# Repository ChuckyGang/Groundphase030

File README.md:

# Groundphase030

This is my test of doing a very VERY simple 030 card for the Amiga 3000/4000 (only tested on 4000)
It breaks all designrules there is.  This is/was just a proof of concept.

it REQUIRES a FPU installed.

Produce cards if you like to or do stuff with this. but please.. OPEN!

Note, this IS a 4 layer board!

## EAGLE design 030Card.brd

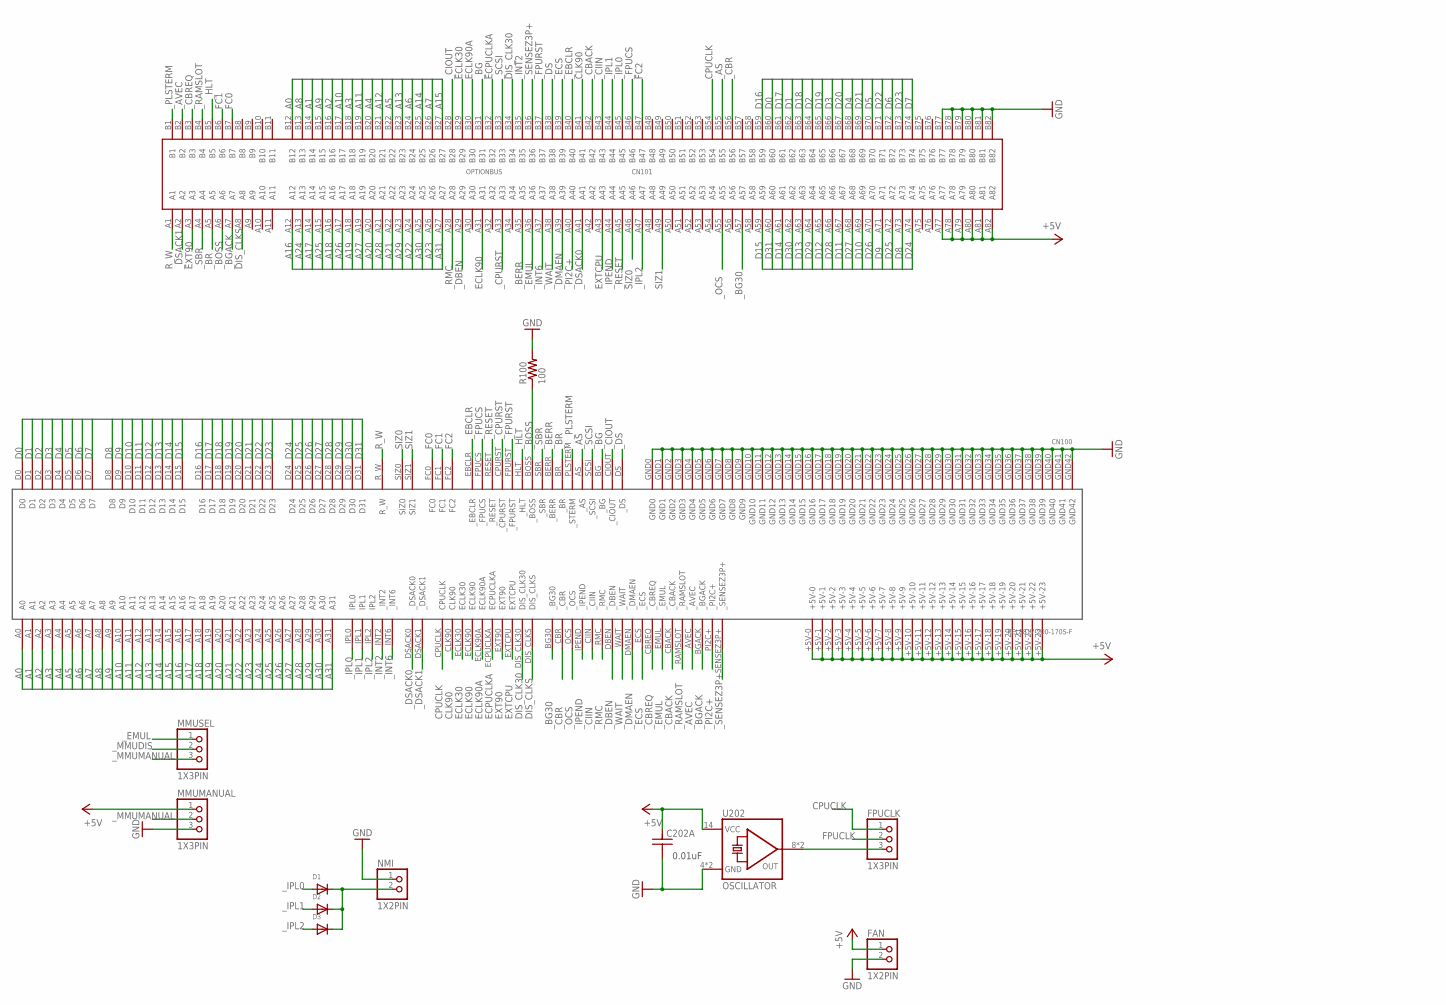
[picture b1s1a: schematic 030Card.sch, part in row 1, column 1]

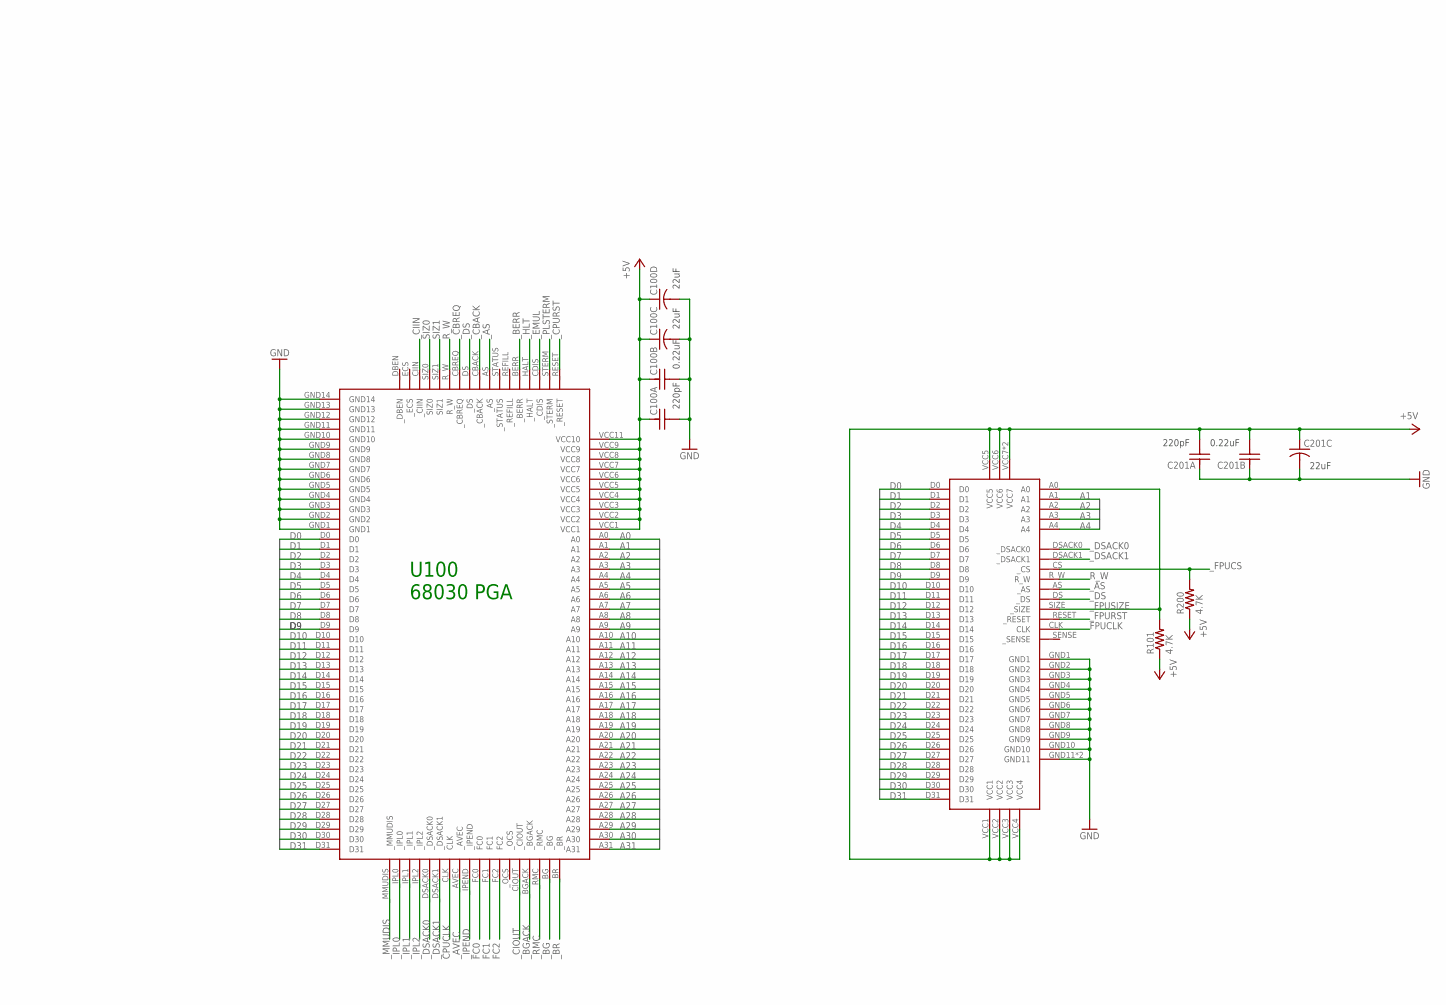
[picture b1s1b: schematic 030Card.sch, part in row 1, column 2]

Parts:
C100A, C201A: 220pF; R0805
C100B, C201B: 0.22uF; R0805
C100C, C100D, C201C: 22uF; SMD-ELECTROLYTE
C202A: 0.01uF; R0805
CN100: KEL8817-200-170S-F
CN101: OPTIONBUS
D1, D2, D3: DIODESOD-323F; SOD-323F
FAN: 1X2PIN
FPUCLK: 1X3PIN
MMUMANUAL: 1X3PIN
MMUSEL: 1X3PIN
NMI: 1X2PIN
R100: 100; R0805
R101, R200: 4.7K; R0805
U100: M68030
U201: M68882PLCC
U202: OSCILLATOR

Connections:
+5V: C100A.1, C100B.1, C100C.+ (1), C100D.+ (1), C201A.2, C201B.2, C201C.+ (1), C202A.1, CN100.+5V-0, CN100.+5V-1, CN100.+5V-2, CN100.+5V-3, CN100.+5V-4, CN100.+5V-5, CN100.+5V-6, CN100.+5V-7, CN100.+5V-8, CN100.+5V-9, CN100.+5V-10, CN100.+5V-11, CN100.+5V-12, CN100.+5V-13, CN100.+5V-14, CN100.+5V-15, CN100.+5V-16, CN100.+5V-17, CN100.+5V-18, CN100.+5V-19, CN100.+5V-20, CN100.+5V-21, CN100.+5V-22, CN100.+5V-23, CN101.A77, CN101.A78, CN101.A79, CN101.A80, CN101.A81, CN101.A82, FAN.1, MMUMANUAL.1, R101.1, R200.1, U100.VCC1, U100.VCC2, U100.VCC3, U100.VCC4, U100.VCC5, U100.VCC6, U100.VCC7, U100.VCC8, U100.VCC9, U100.VCC11 (VCC10), U201.VCC1, U201.VCC2, U201.VCC3, U201.VCC4, U201.VCC5, U201.VCC6, U201.VCC7, U201.VCC8 (VCC7), U202.14 (+5V)
A0: CN100.A0, CN101.B12, U100.A0
A1: CN100.A1, CN101.B14, U100.A1, U201.A1
A2: CN100.A2, CN101.B16, U100.A2, U201.A2
A3: CN100.A3, CN101.B18, U100.A3, U201.A3
A4: CN100.A4, CN101.B20, U100.A4, U201.A4
A5: CN100.A5, CN101.B22, U100.A5
A6: CN100.A6, CN101.B24, U100.A6
A7: CN100.A7, CN101.B26, U100.A7
A8: CN100.A8, CN101.B13, U100.A8
A9: CN100.A9, CN101.B15, U100.A9
A10: CN100.A10, CN101.B17, U100.A10
A11: CN100.A11, CN101.B19, U100.A11
A12: CN100.A12, CN101.B21, U100.A12
A13: CN100.A13, CN101.B23, U100.A13
A14: CN100.A14, CN101.B25, U100.A14
A15: CN100.A15, CN101.B27, U100.A15
A16: CN100.A16, CN101.A12, U100.A16
A17: CN100.A17, CN101.A14, U100.A17
A18: CN100.A18, CN101.A16, U100.A18
A19: CN100.A19, CN101.A18, U100.A19
A20: CN100.A20, CN101.A20, U100.A20
A21: CN100.A21, CN101.A22, U100.A21
A22: CN100.A22, CN101.A24, U100.A22
A23: CN100.A23, CN101.A26, U100.A23
A24: CN100.A24, CN101.A13, U100.A24
A25: CN100.A25, CN101.A15, U100.A25
A26: CN100.A26, CN101.A17, U100.A26
A27: CN100.A27, CN101.A19, U100.A27
A28: CN100.A28, CN101.A21, U100.A28
A29: CN100.A29, CN101.A23, U100.A29
A30: CN100.A30, CN101.A25, U100.A30
A31: CN100.A31, CN101.A27, U100.A31
CLK90: CN100.CLK90, CN101.B41
CPUCLK: CN100.CPUCLK, CN101.B54, FPUCLK.1, U100.CLK
D0: CN100.D0, CN101.B60, U100.D0, U201.D0
D1: CN100.D1, CN101.B62, U100.D1, U201.D1
D2: CN100.D2, CN101.B64, U100.D2, U201.D2
D3: CN100.D3, CN101.B66, U100.D3, U201.D3
D4: CN100.D4, CN101.B68, U100.D4, U201.D4
D5: CN100.D5, CN101.B70, U100.D5, U201.D5
D6: CN100.D6, CN101.B72, U100.D6, U201.D6
D7: CN100.D7, CN101.B74, U100.D7, U201.D7
D8: CN100.D8, CN101.A73, U100.D8, U201.D8
D9: CN100.D9, CN101.A71, U100.D9, U201.D9
D10: CN100.D10, CN101.A69, U100.D10, U201.D10
D11: CN100.D11, CN101.A67, U100.D11, U201.D11
D12: CN100.D12, CN101.A65, U100.D12, U201.D12
D13: CN100.D13, CN101.A63, U100.D13, U201.D13
D14: CN100.D14, CN101.A61, U100.D14, U201.D14
D15: CN100.D15, CN101.A59, U100.D15, U201.D15
D16: CN100.D16, CN101.B59, U100.D16, U201.D16
D17: CN100.D17, CN101.B61, U100.D17, U201.D17
D18: CN100.D18, CN101.B63, U100.D18, U201.D18
D19: CN100.D19, CN101.B65, U100.D19, U201.D19
D20: CN100.D20, CN101.B67, U100.D20, U201.D20
D21: CN100.D21, CN101.B69, U100.D21, U201.D21
D22: CN100.D22, CN101.B71, U100.D22, U201.D22
D23: CN100.D23, CN101.B73, U100.D23, U201.D23
D24: CN100.D24, CN101.A74, U100.D24, U201.D24
D25: CN100.D25, CN101.A72, U100.D25, U201.D25
D26: CN100.D26, CN101.A70, U100.D26, U201.D26
D27: CN100.D27, CN101.A68, U100.D27, U201.D27
D28: CN100.D28, CN101.A66, U100.D28, U201.D28
D29: CN100.D29, CN101.A64, U100.D29, U201.D29
D30: CN100.D30, CN101.A62, U100.D30, U201.D30
D31: CN100.D31, CN101.A60, U100.D31, U201.D31
DIS_CLK30: CN100.DIS_CLK30, CN101.B34
DIS_CLKS: CN100.DIS_CLKS, CN101.A8
ECLK30: CN100.ECLK30, CN101.B29
ECLK90: CN100.ECLK90, CN101.A31
ECLK90A: CN100.ECLK90A, CN101.B30
ECPUCLKA: CN100.ECPUCLKA, CN101.B32
EXT90: CN100.EXT90, CN101.A3
EXTCPU: CN100.EXTCPU, CN101.A43
EXTFPUCLK: FPUCLK.3, U202.8 (OUT), U202.11 (OUT)
FC0: CN100.FC0, CN101.B7, U100.FC0
FC1: CN100.FC1, CN101.B6, U100.FC1
FC2: CN100.FC2, CN101.B47, U100.FC2
FPUCLK: FPUCLK.2, U201.CLK
GND: C100A.2, C100B.2, C100C.- (2), C100D.- (2), C201A.1, C201B.1, C201C.- (2), C202A.2, CN100.GND0, CN100.GND1, CN100.GND2, CN100.GND3, CN100.GND4, CN100.GND5, CN100.GND6, CN100.GND7, CN100.GND8, CN100.GND9, CN100.GND10, CN100.GND11, CN100.GND12, CN100.GND13, CN100.GND14, CN100.GND15, CN100.GND16, CN100.GND17, CN100.GND18, CN100.GND19, CN100.GND20, CN100.GND21, CN100.GND22, CN100.GND23, CN100.GND24, CN100.GND25, CN100.GND26, CN100.GND27, CN100.GND28, CN100.GND29, CN100.GND30, CN100.GND31, CN100.GND32, CN100.GND33, CN100.GND34, CN100.GND35, CN100.GND36, CN100.GND37, CN100.GND38, CN100.GND39, CN100.GND40, CN100.GND41, CN100.GND42, CN101.B77, CN101.B78, CN101.B79, CN101.B80, CN101.B81, CN101.B82, FAN.2, MMUMANUAL.3, NMI.1, R100.2, U100.GND1, U100.GND2, U100.GND3, U100.GND4, U100.GND5, U100.GND6, U100.GND7, U100.GND8, U100.GND9, U100.GND10, U100.GND11, U100.GND12, U100.GND13, U100.GND14, U201.GND1, U201.GND2, U201.GND3, U201.GND4, U201.GND5, U201.GND6, U201.GND7, U201.GND8, U201.GND9, U201.GND10, U201.GND11, U201.GND12 (GND11), U202.4 (GND), U202.7 (GND)
R_W: CN100.R_W, CN101.A1, U100.R_W, U201.R_W
SIZ0: CN100.SIZ0, CN101.A46, U100.SIZ0
SIZ1: CN100.SIZ1, CN101.A49, U100.SIZ1
_AS: CN100._AS, CN101.B55, U100._AS, U201._AS
_AVEC: CN100._AVEC, CN101.B2, U100._AVEC
_BERR: CN100._BERR, CN101.A35, U100._BERR
_BG: CN100._BG, CN101.B31, U100._BG
_BG30: CN100._BG30, CN101.A57
_BGACK: CN100._BGACK, CN101.A7, U100._BGACK
_BOSS: CN100._BOSS, CN101.A6, R100.1
_BR: CN100._BR, CN101.A5, U100._BR
_CBACK: CN100._CBACK, CN101.B42, U100._CBACK
_CBR: CN100._CBR, CN101.B56
_CBREQ: CN100._CBREQ, CN101.B3, U100._CBREQ
_CIIN: CN100._CIIN, CN101.B43, U100._CIIN
_CIOUT: CN100._CIOUT, CN101.B28, U100._CIOUT
_CPURST: CN100._CPURST, CN101.A33, U100._RESET
_DBEN: CN100._DBEN, CN101.A29
_DMAEN: CN100._DMAEN, CN101.A39
_DS: CN100._DS, CN101.B38, U100._DS, U201._DS
_DSACK0: CN100._DSACK0, CN101.A41, U100._DSACK0, U201._DSACK0
_DSACK1: CN100._DSACK1, CN101.A2, U100._DSACK1, U201._DSACK1
_EBCLR: CN100._EBCLR, CN101.B40
_ECS: CN100._ECS, CN101.B39
_EMUL: CN100._EMUL, CN101.A36, MMUSEL.1, U100._CDIS
_FPUCS: CN100._FPUCS, CN101.B46, R200.2, U201._CS
_FPURST: CN100._FPURST, CN101.B37, U201._RESET
_FPUSIZE: R101.2, U201.A0, U201.SIZE (_SIZE)
_HLT: CN100._HLT, CN101.B5, U100._HALT
_INT2: CN100._INT2, CN101.B35
_INT6: CN100._INT6, CN101.A37
_IPEND: CN100._IPEND, CN101.A44, U100._IPEND
_IPL0: CN100._IPL0 (IPL0), CN101.B45, D1.A, U100._IPL0
_IPL1: CN100._IPL1 (IPL1), CN101.B44, D2.A, U100._IPL1
_IPL2: CN100._IPL2 (IPL2), CN101.A47, D3.A, U100._IPL2
_MMUDIS: MMUSEL.2, U100._MMUDIS
_MMUMANUAL: MMUMANUAL.2, MMUSEL.3
_NMI: D1.C, D2.C, D3.C, NMI.2
_OCS: CN100._OCS, CN101.A55
_PI2C+: CN100._PI2C+, CN101.A40
_PLSTERM: CN100._PLSTERM (_STERM), CN101.B1, U100._STERM
_RAMSLOT: CN100._RAMSLOT, CN101.B4
_RESET: CN100._RESET, CN101.A45
_RMC: CN100._RMC, CN101.A28, U100._RMC
_SBR: CN100._SBR, CN101.A4
_SCSI: CN100._SCSI, CN101.B33
_SENSEZ3P+: CN100._SENSEZ3P+, CN101.B36
_WAIT: CN100._WAIT, CN101.A38

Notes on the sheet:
U100 68030 PGA

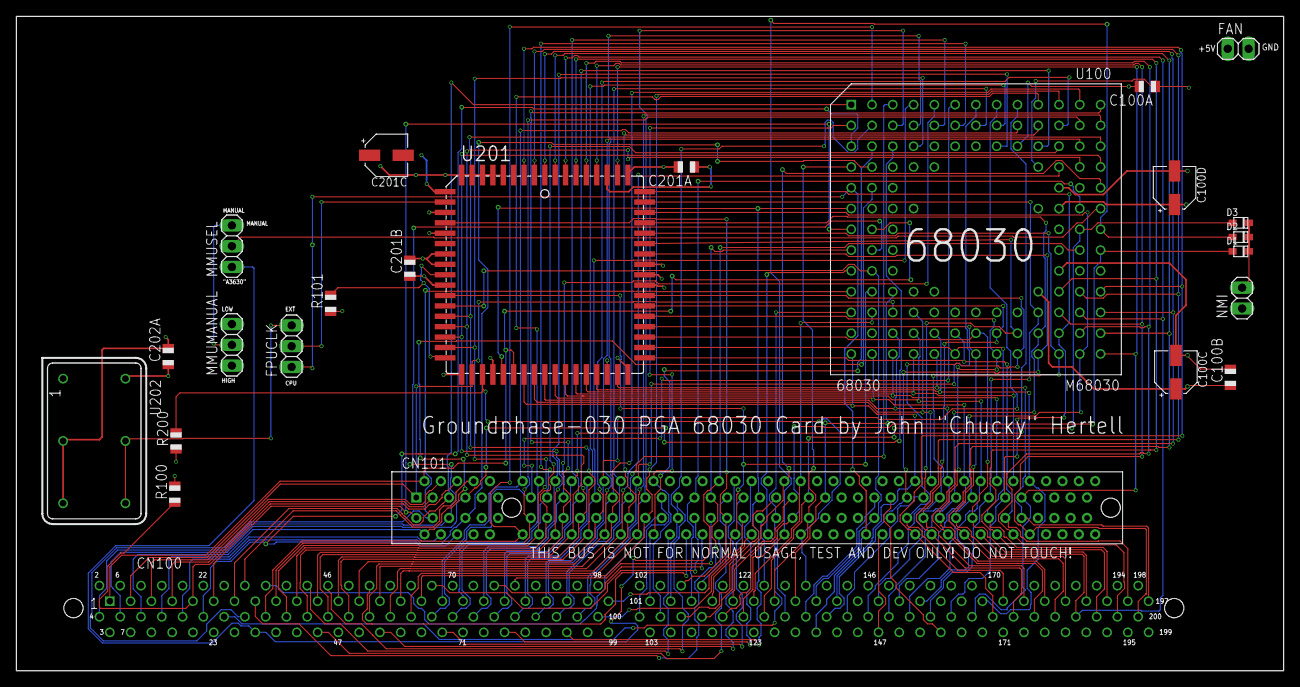
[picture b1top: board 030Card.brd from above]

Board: 4 copper layers, 154.9 x 80.0 mm, 24 parts (0 on the bottom side), 129 nets.

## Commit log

2019-05-18 Initial publication. Groundphase 030. a simple PGA 030 card for the Amiga 3000/4000 (only tested on 4000). might break all designrules there ever is. this is just me playing around with an idea I had.
    please do stuff.. BUT OPEN!
2019-05-18 Changed Readme file
2019-05-18 Fixed readme even more
